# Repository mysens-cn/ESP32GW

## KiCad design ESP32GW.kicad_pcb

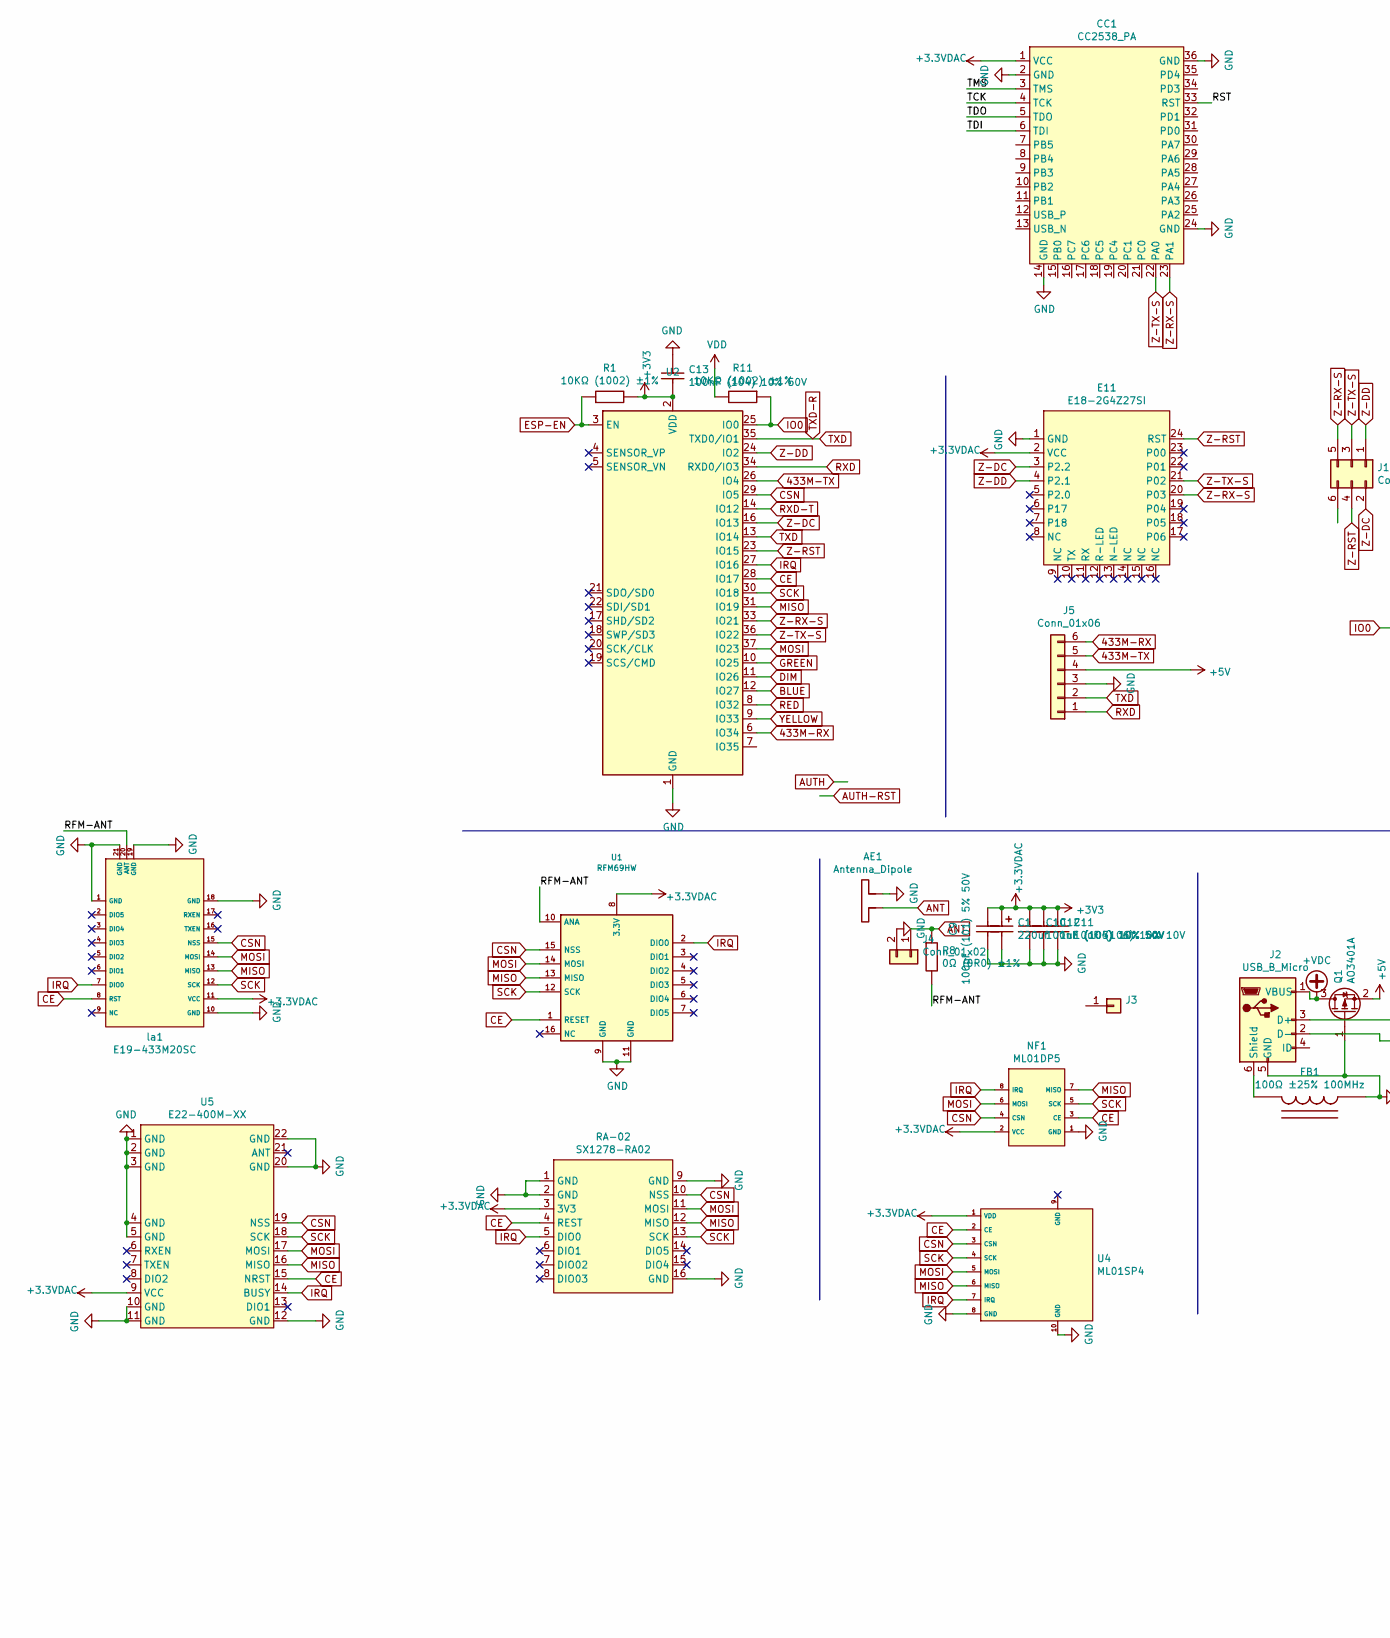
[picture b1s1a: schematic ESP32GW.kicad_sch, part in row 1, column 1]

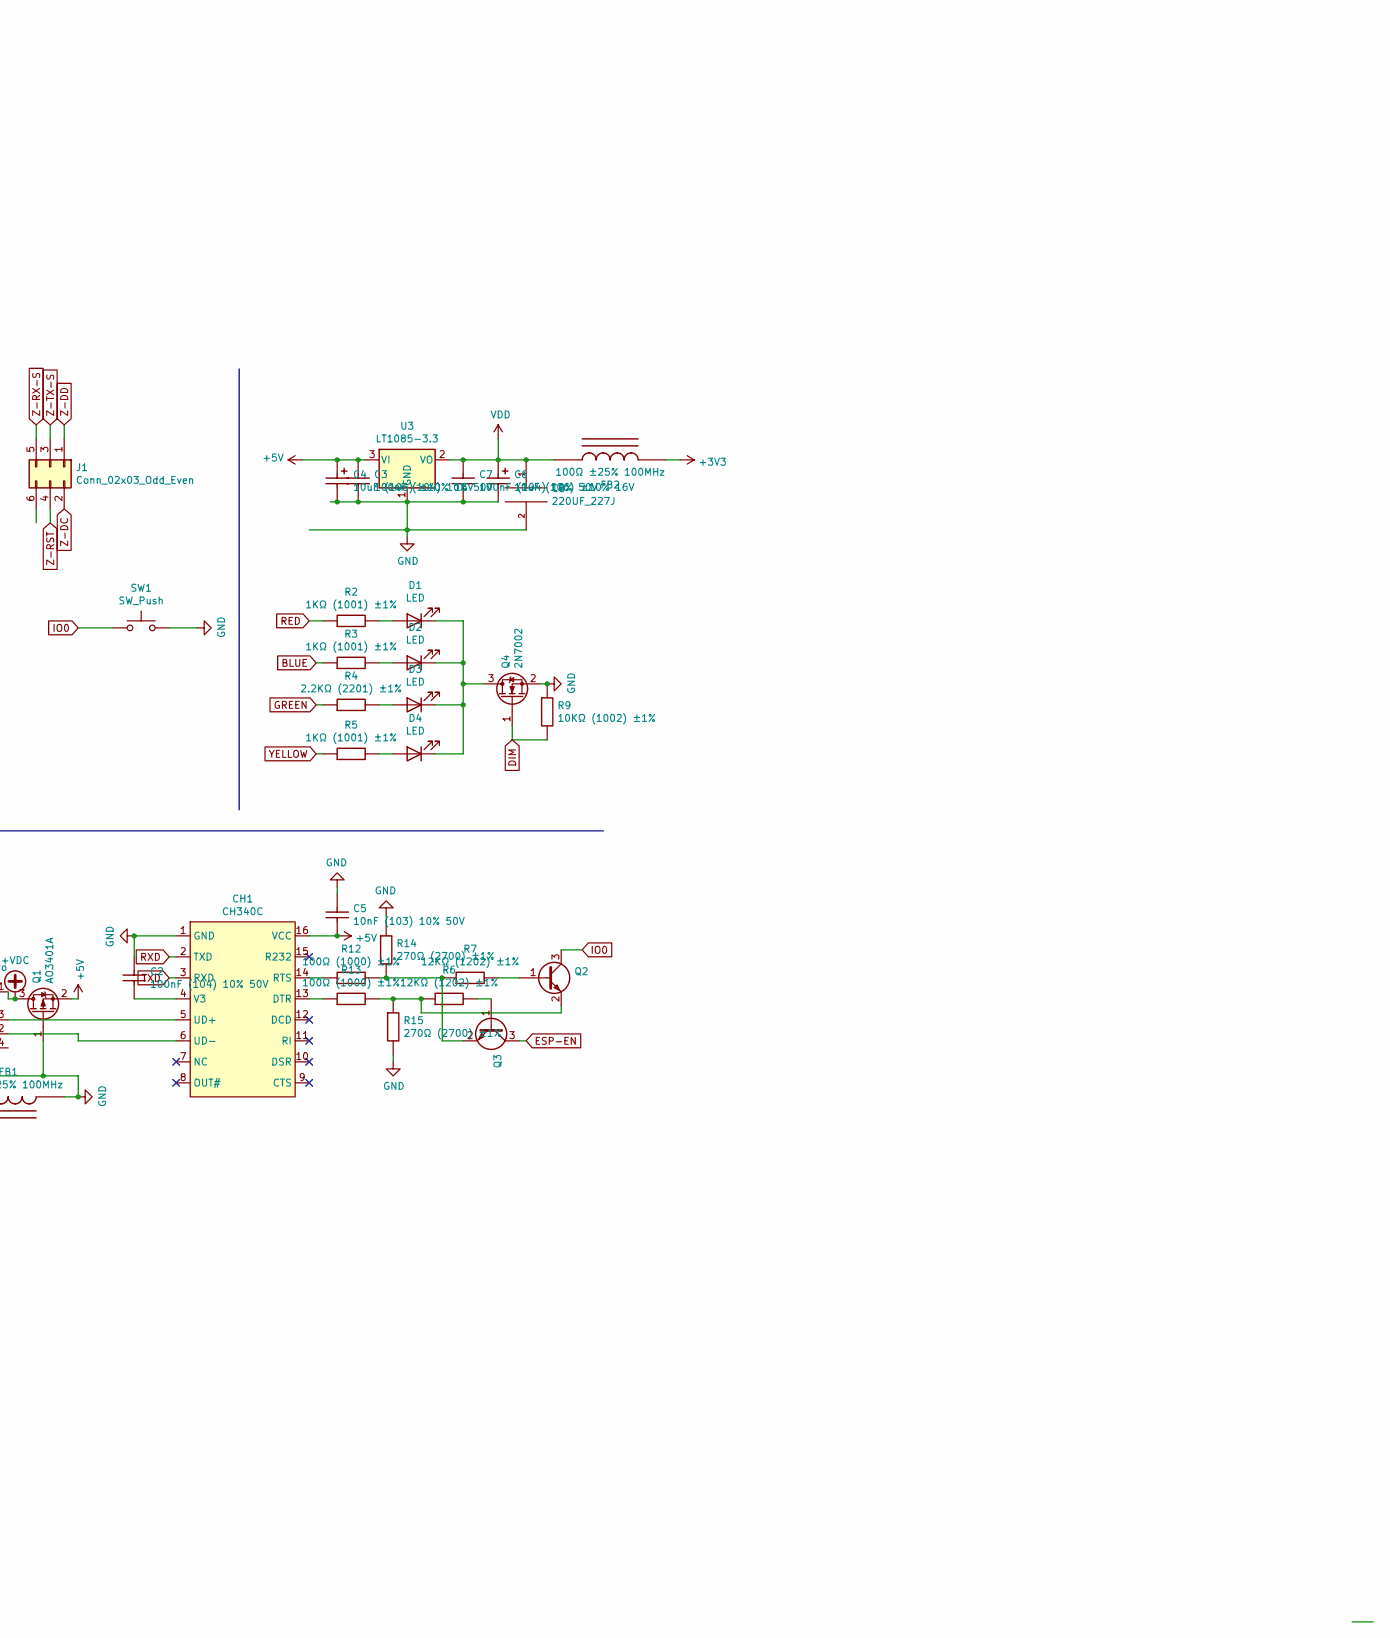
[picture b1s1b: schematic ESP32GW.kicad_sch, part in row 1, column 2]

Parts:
AE1: Antenna_Dipole; SMA_Samtec_SMA-J-P-H-ST-EM1_EdgeMount
C1: 220uF__50V; CASE-C_6032
C2, C3, C7, C10, C13: 0603_100nF__104_10%_50V; 0603_C
C4, C6: 3216_10uF__106_10%_16V; CASE-A_3216
C5: 0603_10nF__103_10%_50V; 0603_C
C8: 220UF_227J; CASE-C_6032
C9: 0603_100pF__101_5%_50V; 0603_C
C11: 0603_10uF__106_10%_10V; 0603_C
C12: 0603_1uF__105_10%_50V; 0603_C
CC1: CC2538_PA
CH1: CH340C; SOP-16_150MIL
D1, D2, D3, D4: LED; LED_D3.0mm
E11: E18-2G4Z27SI
FB1: 0805_100Ω_25%_100MHz; 0805_L
FB2: GZ2012D101TF1; 0805_L
J1: Conn_02x03_Odd_Even; PinSocket_2x03_P2.54mm_Vertical
J2: USB_B_Micro; USB_Micro-B
J3: Conn_01x01; dingweikong
J4: Conn_01x02; ALS-PT19
J5: Conn_01x06; 2.5-6P-kit
NF1: ML01DP5; E01-ML01DP5
Q1: AO3401A; SOT-23-3L
Q2, Q3: J3Y-Transistor_BJT; SOT-23(SOT-23-3)
Q4: 2N7002; SOT-23(SOT-23-3)
R1, R9, R11: 0603_10KΩ__1002_1%; 0603_R
R2, R3, R5: 0603_1KΩ__1001_1%; 0603_R
R4: 0603_2.2KΩ__2201_1%; 0603_R
R6, R7: 0603_12KΩ__1202_1%; 0603_R
R8: 0603_0Ω__0R0_1%; 0603
R12, R13: 0603_100Ω__1000_1%; 0603_R
R14, R15: 0603_270Ω__2700_1%; 0603_R
RA-02: SX1278-RA02; SX1278-Ra02
SW1: SW_Push; TS-D008
U1: RFM69HW; RFM69HW_SMD
U2: ESP32-WROOM-32D; ESP32-WROOM-32
U3: LT1085-3.3; TO-252-2
U4: ML01SP4; E01-ML01SP4
U5: E22-400M-XX; E22-400M20S
la1: E19-433M20SC

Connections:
433M-RX: J5.6, U2.6 (IO34)
433M-TX: J5.5, U2.26 (IO4)
+3.3VDAC: C1.1, C9.2, C10.1, C11.1, C12.1, C13.2, CC1.1 (VCC), E11.2 (VCC), FB2.2, NF1.2 (VCC), R1.2, RA-02.3 (3V3), U1.8 (3.3V), U2.2 (VDD), U4.1 (VDD), U5.9 (VCC), la1.11 (VCC); also elsewhere on the board
+5V: C3.1, C4.1, C5.2, CH1.16 (VCC), J5.4, Q1.2 (S), U3.3 (VI)
+VDC: J2.1 (VBUS), Q1.3 (D)
/RFM-ANT: R8.2, U1.10 (ANA), la1.20 (ANT)
/RST: CC1.7 (PB5), CC1.33 (RST)
/TCK: CC1.4 (TCK)
/TDI: CC1.6 (TDI)
/TDO: CC1.5 (TDO)
/TMS: CC1.3 (TMS)
ANT: AE1.1, J4.1, R8.1
BLUE: R3.1, U2.12 (IO27)
CE: NF1.3 (CE), RA-02.4 (REST), U1.1 (RESET), U2.28 (IO17), U4.2 (CE), U5.15 (NRST), la1.8 (RST)
CSN: NF1.4 (CSN), RA-02.10 (NSS), U1.15 (NSS), U2.29 (IO5), U4.3 (CSN), U5.19 (NSS), la1.15 (NSS)
DIM: Q4.1 (G), R9.2, U2.11 (IO26)
ESP-EN: Q3.3, R1.1, U2.3 (EN)
GND: AE1.2, C1.2, C2.1, C3.2, C4.2, C5.1, C6.2, C7.2, C8.2, C9.1, C10.2, C11.2, C12.2, C13.1, CC1.2 (GND), CC1.14 (GND), CC1.24 (GND), CC1.36 (GND), CH1.1 (GND), E11.1 (GND), FB1.1, J2.5 (GND), J4.2, J5.3, NF1.1 (GND), Q1.1 (G), Q4.2 (S), R9.1, R14.1, R15.2, RA-02.1 (GND), RA-02.2 (GND), RA-02.9 (GND), RA-02.16 (GND), SW1.2, U1.9 (GND), U1.11 (GND), U2.1 (GND), U2.15 (GND), U2.38 (GND), U2.39 (GND), U3.1 (GND), U4.8 (GND), U4.10 (GND), U5.1 (GND), U5.2 (GND), U5.3 (GND), U5.4 (GND), U5.5 (GND), U5.10 (GND), U5.11 (GND), U5.12 (GND), U5.20 (GND), U5.22 (GND), la1.1 (GND), la1.10 (GND), la1.18 (GND), la1.19 (GND), la1.21 (GND); also elsewhere on the board
GREEN: R4.1, U2.10 (IO25)
IO0: Q2.3, R11.1, SW1.1, U2.25 (IO0)
IRQ: NF1.8 (IRQ), RA-02.5 (DIO0), U1.2 (DIO0), U2.27 (IO16), U4.7 (IRQ), U5.14 (BUSY), la1.7 (DIO0)
MISO: NF1.7 (MISO), RA-02.12 (MISO), U1.13 (MISO), U2.31 (IO19), U4.6 (MISO), U5.16 (MISO), la1.13 (MISO)
MOSI: NF1.6 (MOSI), RA-02.11 (MOSI), U1.14 (MOSI), U2.37 (IO23), U4.5 (MOSI), U5.17 (MOSI), la1.14 (MOSI)
unnamed: C2.2, CH1.4 (V3)
unnamed: CH1.5 (UD+), J2.3 (D+)
unnamed: CH1.6 (UD-), J2.2 (D-)
unnamed: CH1.13 (DTR), R13.1
unnamed: CH1.14 (RTS), R12.1
unnamed: D1.1 (K), D2.1 (K), D3.1 (K), D4.1 (K), Q4.3 (D)
unnamed: D1.2 (A), R2.2
unnamed: D2.2 (A), R3.2
unnamed: D3.2 (A), R4.2
unnamed: D4.2 (A), R5.2
unnamed: FB1.2, J2.6 (Shield)
unnamed: Q2.1, R7.2
unnamed: Q2.2, R6.1, R13.2, R15.1
unnamed: Q3.1, R6.2
unnamed: Q3.2, R7.1, R12.2, R14.2
RED: R2.1, U2.8 (IO32)
RXD: CH1.2 (TXD), J5.1, U2.34 (RXD0/IO3)
RXD-T: U2.14 (IO12)
SCK: NF1.5 (SCK), RA-02.13 (SCK), U1.12 (SCK), U2.30 (IO18), U4.4 (SCK), U5.18 (SCK), la1.12 (SCK)
TXD: CH1.3 (RXD), J5.2, U2.13 (IO14), U2.35 (TXD0/IO1)
VDD: C6.1, C7.1, C8.1, FB2.1, R11.2, U3.2 (VO)
YELLOW: R5.1, U2.9 (IO33)
Z-DC: E11.3 (P2.2), J1.2, U2.16 (IO13)
Z-DD: E11.4 (P2.1), J1.1, U2.24 (IO2)
Z-RST: E11.24 (RST), J1.4, U2.23 (IO15)
Z-RX-S: CC1.23 (PA1), E11.20 (P03), J1.5, U2.33 (IO21)
Z-TX-S: CC1.22 (PA0), E11.21 (P02), J1.3, U2.36 (IO22)

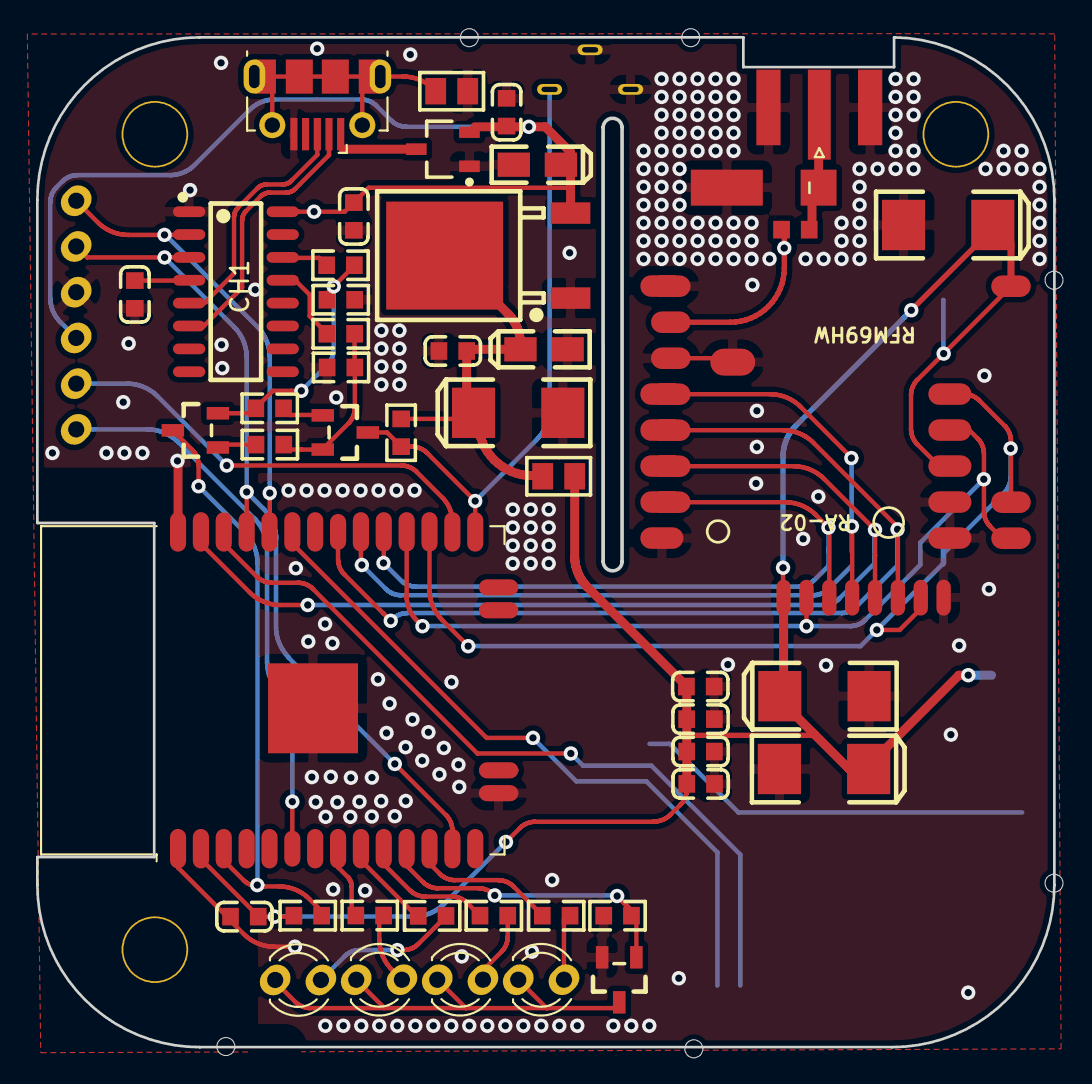
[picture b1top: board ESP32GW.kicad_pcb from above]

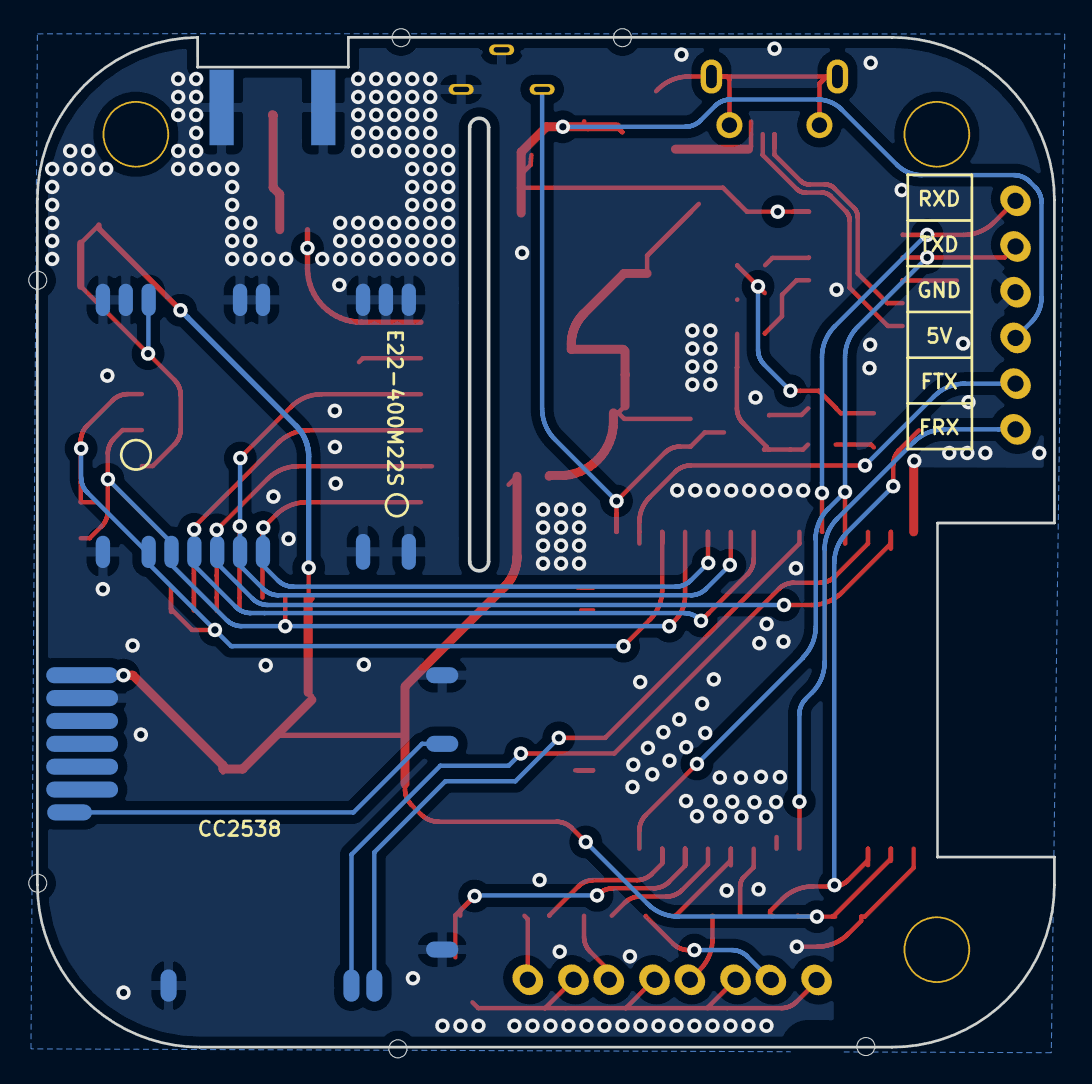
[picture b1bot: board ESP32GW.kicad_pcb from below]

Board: 2 copper layers, 56.5 x 56.1 mm, 62 parts (3 on the bottom side), 42 nets.

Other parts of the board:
C1#2, C1#3: 220uF__50V; CASE-C_6032
J3#2, J3#3, J3#4, J3#5, J3#6, J3#7, J3#8, J3#9, J3#10: Conn_01x01; dingweikong

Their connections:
+3.3VDAC: C1#2.1, C1#3.1; also elsewhere on the board
GND: C1#2.2, C1#3.2; also elsewhere on the board

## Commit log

2020-08-20 frist up
